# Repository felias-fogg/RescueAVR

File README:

This Arduino sketch is an alternative firmware for manekinen's Fusebit
Doctor PCB (see http://mdiy.pl/atmega-fusebit-doctor-hvpp/?lang=en). The
functionality is very similar. However, it is Open Source (under the
GPL)  and can be freely modified and extended.

You can install the firmware by simply uploading the HEX file to an
ATmega328(P) and deactivating the fuse CKDIV8, so that the chip runs
on 8MHz. Now you are all set.

You can either use the board interactively or stand alone. 

Stand alone mode: After power-up, all LEDs are off and you can insert
a chip. After pressing the button, the board will first try to
recognize the chip. If successful, the green LED will be on for 3
secs, if unsuccessful (chip unknown or completely broken), the red
light will be on for 3 secs. In the rare case that the chip is known,
but we do not know the default fuses, first the green LED is on for 1
second, then the red LED is on for 3 seconds. After that, the board
tries to reset all lock bits and then tries to set the fuses to a safe
default setting. If successful, the green LED blinks, otherwise the
red LED blinks. If unsuccessful, you can try to set the erase jumper,
which allows for erasing the entire chip in order to recover it.

Interactive mode: Set your terminal to 19200 baud, no parity, 1
stop-bit. The board tries to recognize the chip after pressing the
button and then allows you to interactively change any fuse or lock,
to reset the fuses to its default value, or to erase the chip. If the
chip is unknown, it will still recogize a chip signature. If you know
how many fuse bytes the chip has, you can specify that and continue
from there in order to manually change the fuses to desirable values
(look into the manual!). If the board cannot detect any chip, you
still can try to send the commands to the chip. Specify the protocol:
HVPP for all ATmega chips, HVPP for Tiny for all MCUs from the
ATtiny2313 and ATtiny26(1) family, and HVSP for all the other ATtiny
chips. 

If you want to change the firmware, you can do this using the Arduino
IDE. In order to do so, you first need to install a bootloader. Since
the ATmega is running on 8 MHz, you need to use the bootloader
ATmegaBOOT_168_atmega328_pro_8MHz.hex (for your ATmega328P) or
ATmegaBOOT_168_pro_8MHz.hex (if you use an ATmega168). You also should
set the fuse BOOTRST (enabling the boot reset vector) and set the boot
loader size to 2048 bytes in the fuses. Now you can put the chip onto
the fusebit doctor board and connect via a serial line to your
computer. Once you have registered this serial line with your Arduino
IDE and have chosen "Arduino Pro or Pro Mini (3.3V 8MHz) w/ ATmega328"
as the board you want to work with, you can start to download sketches
to the board. Note that you always have to press the reset button in
order to enable the transfer of the program from your computer to the
chip. The timing is critical here. Press the button immediately after
the compiler has finished its work!

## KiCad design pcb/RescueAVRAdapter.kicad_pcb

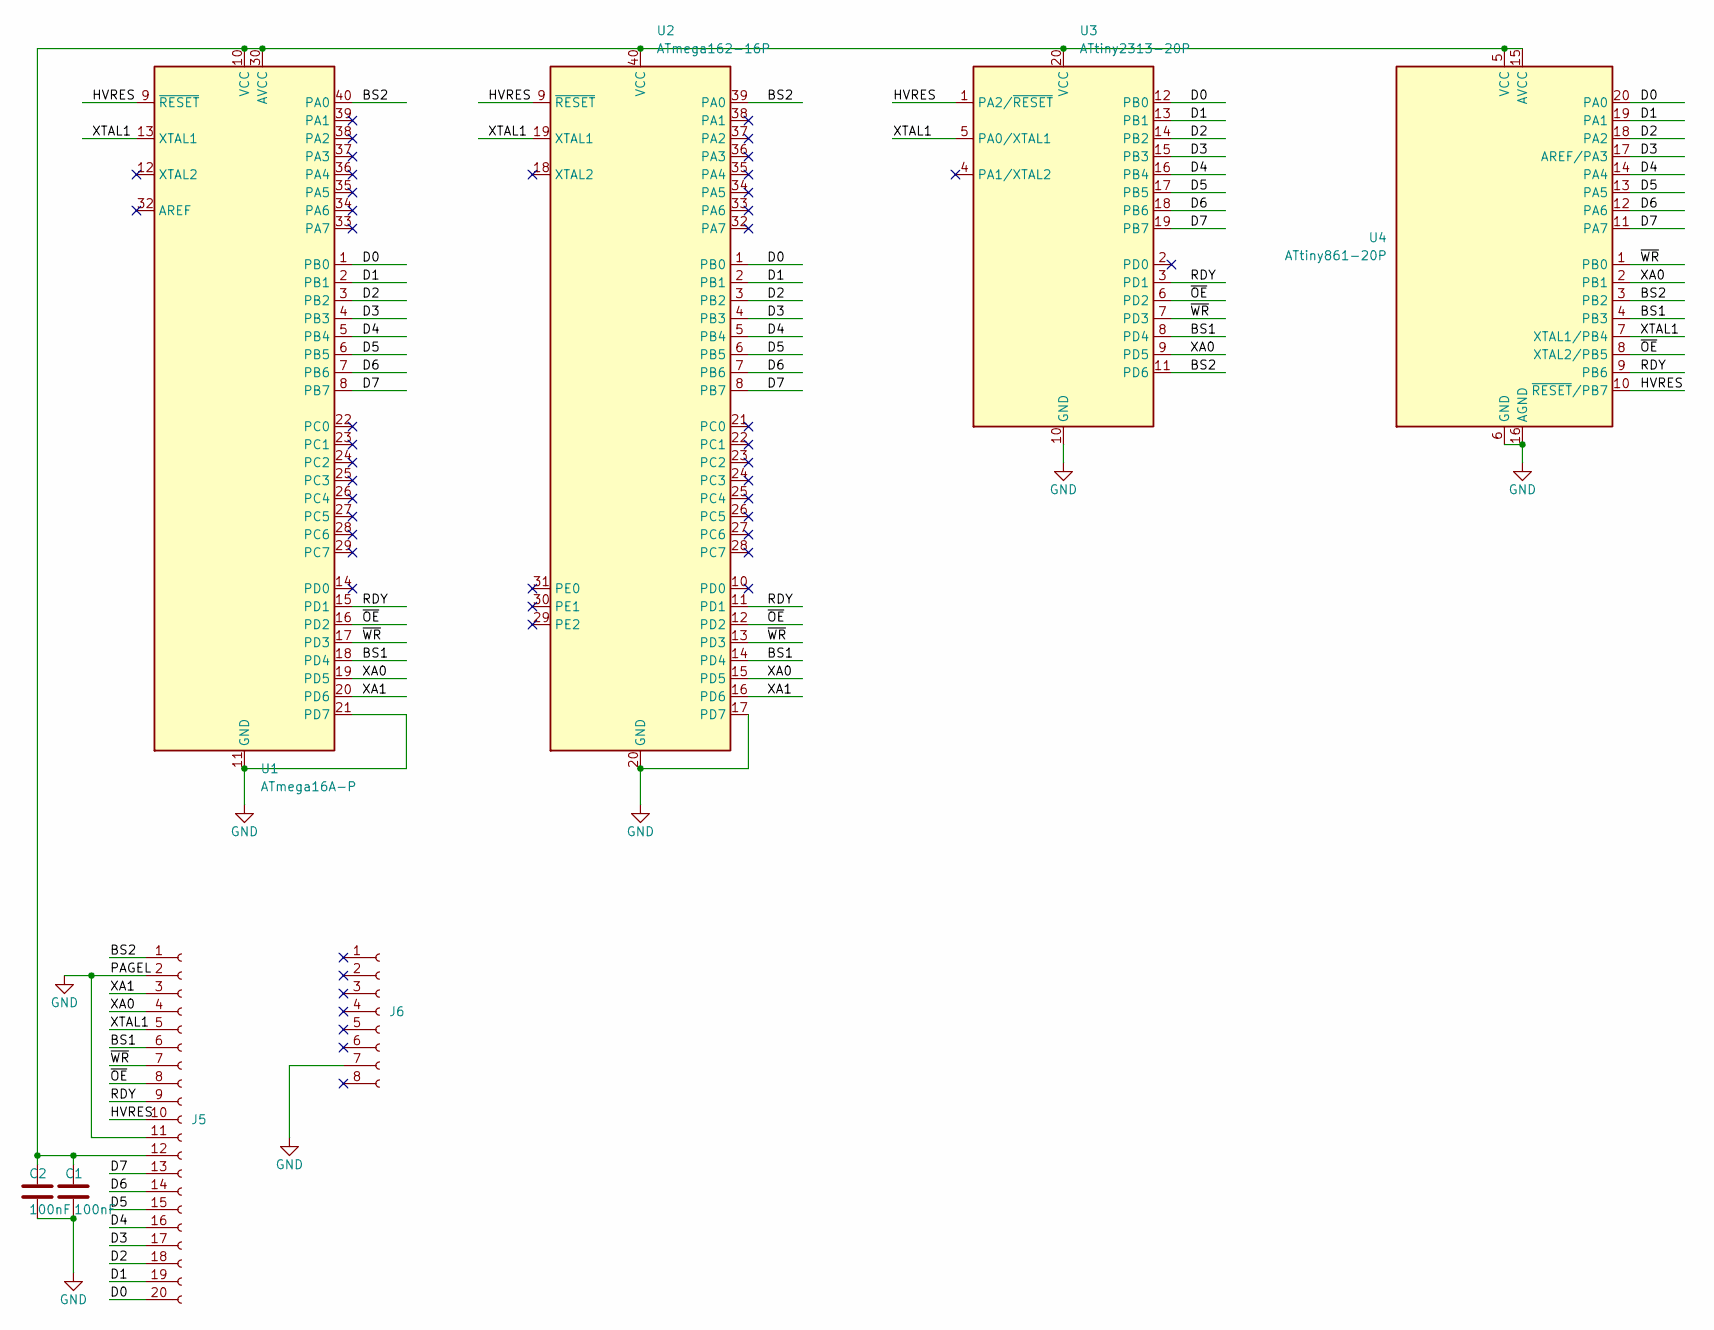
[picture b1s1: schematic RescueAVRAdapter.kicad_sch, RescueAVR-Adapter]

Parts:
C1, C2: 100nF; C_Disc_D7.5mm_W2.5mm_P5.00mm
J5: Conn_01x20_Socket; PinHeader_1x20_P2.54mm_Vertical
J6: Conn_01x08_Socket; PinHeader_1x08_P2.54mm_Vertical
U1: ATmega16A-P; DIP-40_W15.24mm_Socket
U2: ATmega162-16P; DIP-40_W15.24mm_Socket
U3: ATtiny2313-20P; DIP-20_W7.62mm_Socket
U4: ATtiny861-20P; DIP-20_W7.62mm_Socket

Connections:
/BS1: J5.6, U1.18 (PD4), U2.14 (PD4), U3.8 (PD4), U4.4 (PB3)
/BS2: J5.1, U1.40 (PA0), U2.39 (PA0), U3.11 (PD6), U4.3 (PB2)
/D0: J5.20, U1.1 (PB0), U2.1 (PB0), U3.12 (PB0), U4.20 (PA0)
/D1: J5.19, U1.2 (PB1), U2.2 (PB1), U3.13 (PB1), U4.19 (PA1)
/D2: J5.18, U1.3 (PB2), U2.3 (PB2), U3.14 (PB2), U4.18 (PA2)
/D3: J5.17, U1.4 (PB3), U2.4 (PB3), U3.15 (PB3), U4.17 (AREF/PA3)
/D4: J5.16, U1.5 (PB4), U2.5 (PB4), U3.16 (PB4), U4.14 (PA4)
/D5: J5.15, U1.6 (PB5), U2.6 (PB5), U3.17 (PB5), U4.13 (PA5)
/D6: J5.14, U1.7 (PB6), U2.7 (PB6), U3.18 (PB6), U4.12 (PA6)
/D7: J5.13, U1.8 (PB7), U2.8 (PB7), U3.19 (PB7), U4.11 (PA7)
/HVRES: J5.10, U1.9 (~RESET), U2.9 (~RESET), U3.1 (PA2/~RESET), U4.10 (~RESET/PB7)
/RDY: J5.9, U1.15 (PD1), U2.11 (PD1), U3.3 (PD1), U4.9 (PB6)
/XA0: J5.4, U1.19 (PD5), U2.15 (PD5), U3.9 (PD5), U4.2 (PB1)
/XA1: J5.3, U1.20 (PD6), U2.16 (PD6)
/XTAL1: J5.5, U1.13 (XTAL1), U2.19 (XTAL1), U3.5 (PA0/XTAL1), U4.7 (XTAL1/PB4)
/~OE: J5.8, U1.16 (PD2), U2.12 (PD2), U3.6 (PD2), U4.8 (XTAL2/PB5)
/~WR: J5.7, U1.17 (PD3), U2.13 (PD3), U3.7 (PD3), U4.1 (PB0)
GND: C1.2, C2.2, J5.2, J5.11, J6.7, U1.11 (GND), U1.21 (PD7), U1.31 (GND), U2.17 (PD7), U2.20 (GND), U3.10 (GND), U4.6 (GND), U4.16 (AGND)
unnamed: C1.1, C2.1, J5.12, U1.10 (VCC), U1.30 (AVCC), U2.40 (VCC), U3.20 (VCC), U4.5 (VCC), U4.15 (AVCC)

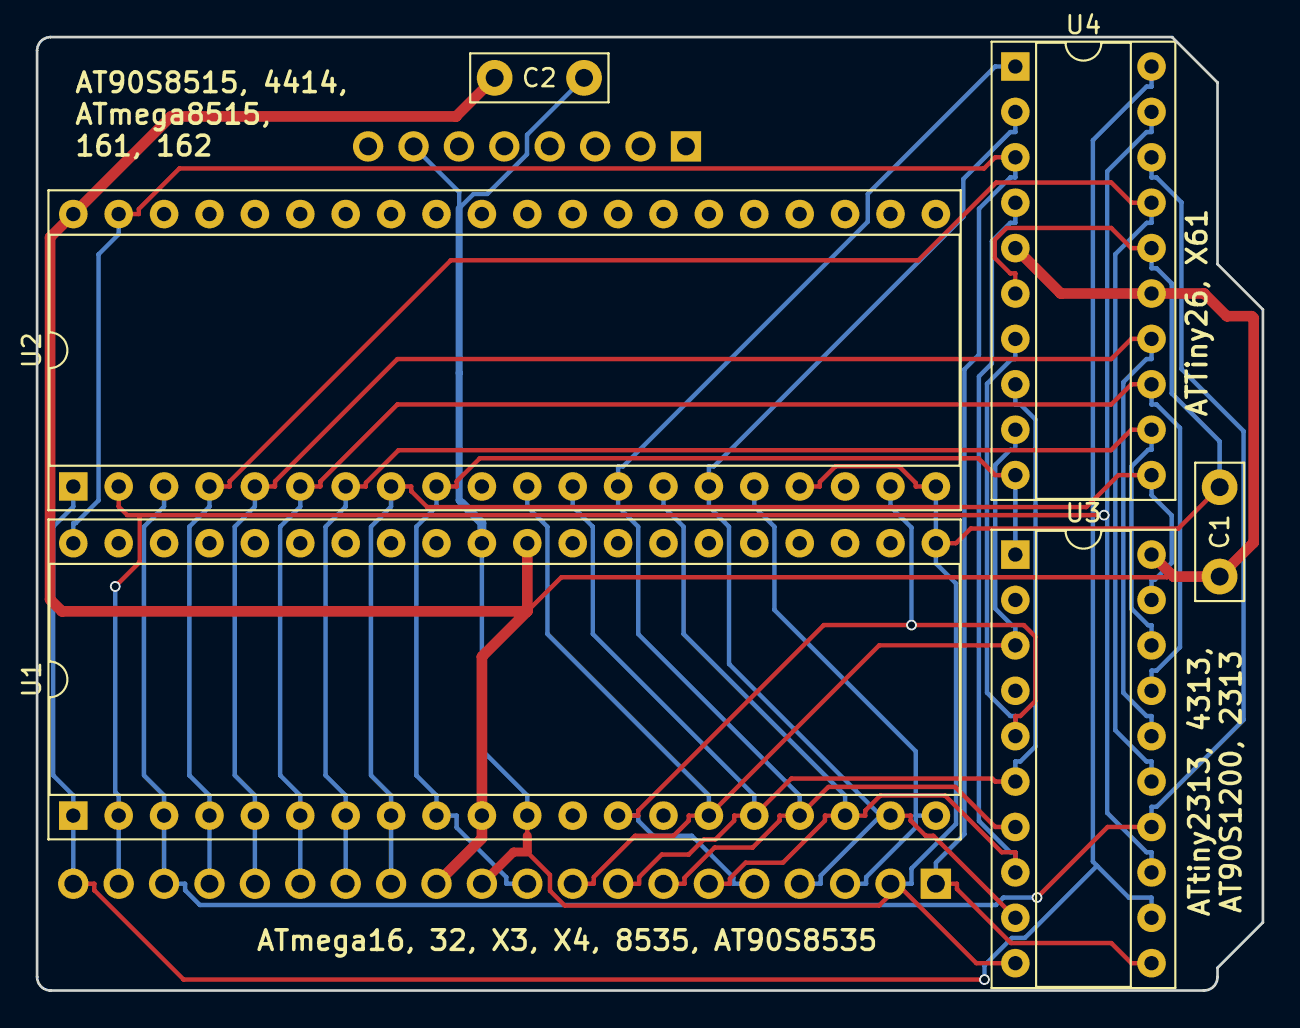
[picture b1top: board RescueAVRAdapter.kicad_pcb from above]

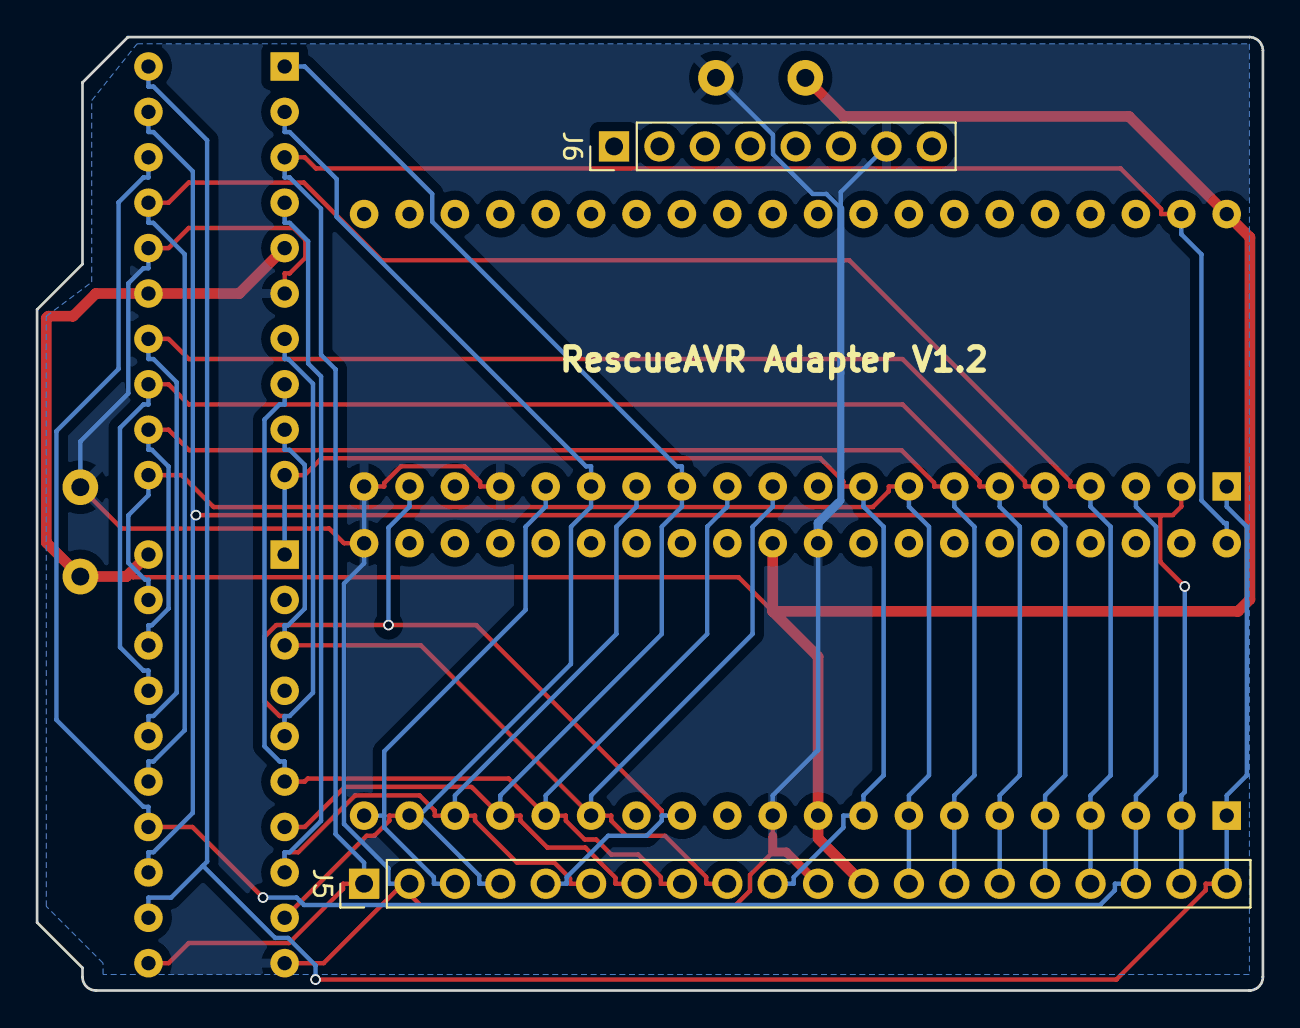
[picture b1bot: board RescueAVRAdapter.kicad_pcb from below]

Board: 2 copper layers, 68.6 x 53.3 mm, 8 parts (2 on the bottom side), 19 nets.

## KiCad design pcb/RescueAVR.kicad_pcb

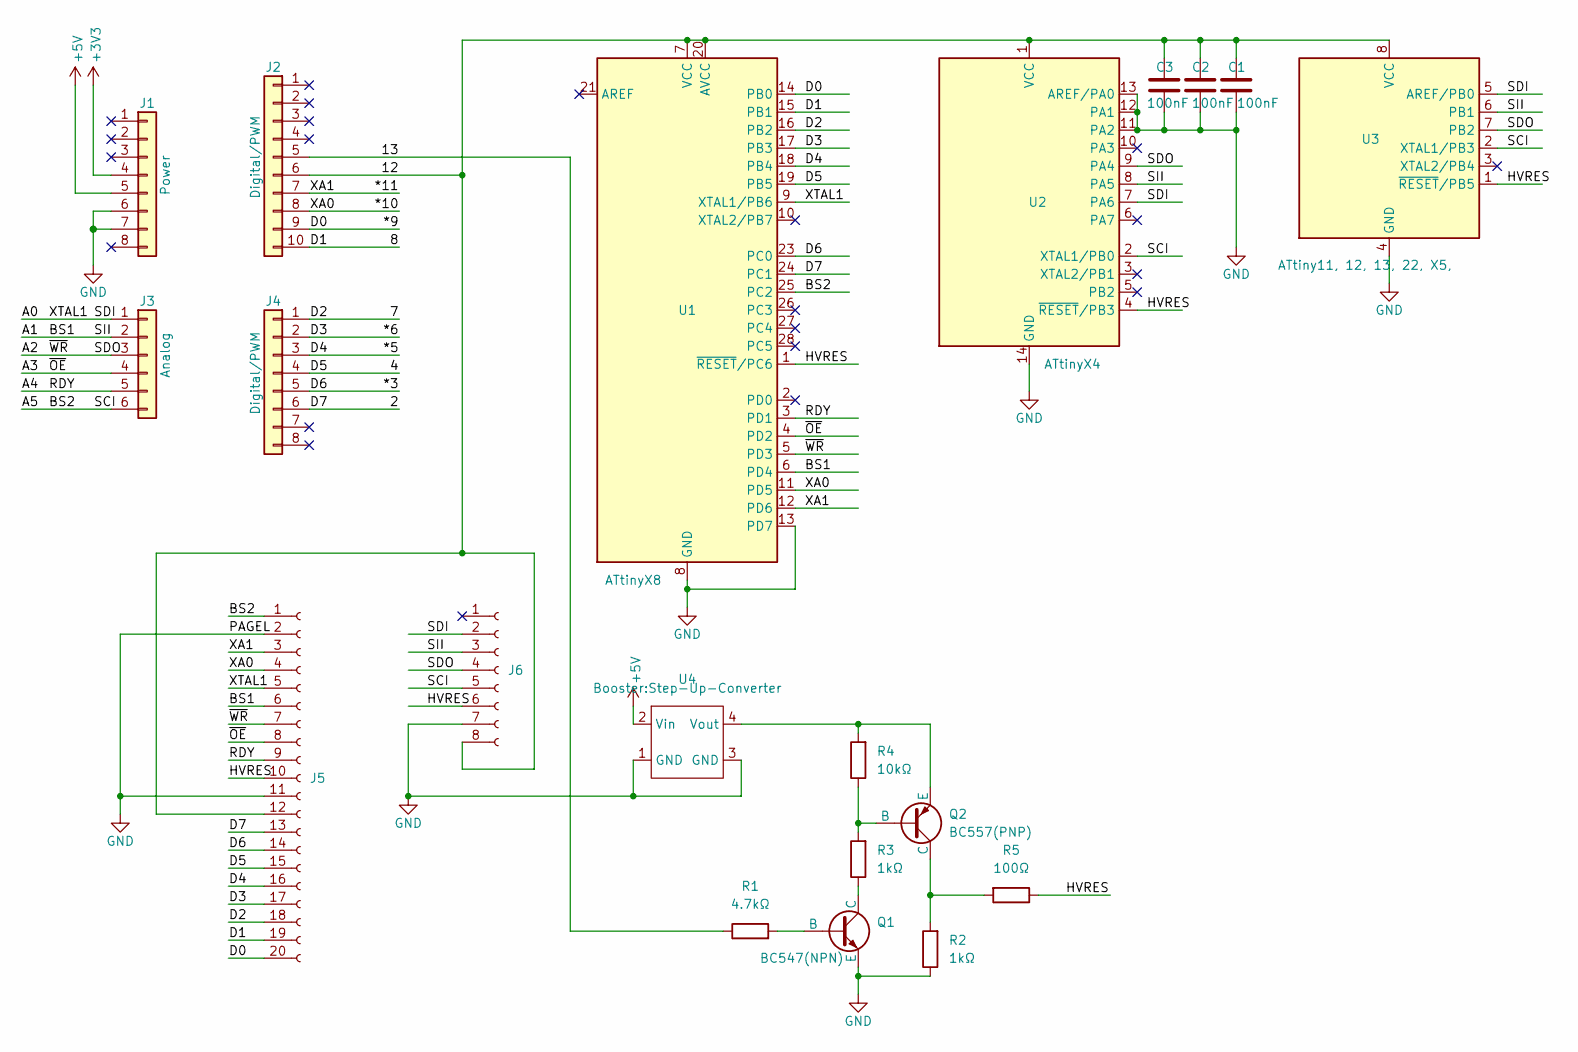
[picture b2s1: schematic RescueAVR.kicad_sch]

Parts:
C1, C2, C3: 100nF; C_Disc_D7.5mm_W2.5mm_P5.00mm
J1: Power; PinHeader_1x08_P2.54mm_Vertical
J2: Digital/PWM; PinHeader_1x10_P2.54mm_Vertical
J3: Analog; PinHeader_1x06_P2.54mm_Vertical
J4: Digital/PWM; PinHeader_1x08_P2.54mm_Vertical
J5: Conn_01x20_Socket; PinSocket_1x20_P2.54mm_Vertical
J6: Conn_01x08_Socket; PinSocket_1x08_P2.54mm_Vertical
Q1: BC547(NPN); TO-92
Q2: BC557(PNP); TO-92
R1: 4.7kΩ; R_Axial_DIN0204_L3.6mm_D1.6mm_P7.62mm_Horizontal
R2, R3: 1kΩ; R_Axial_DIN0204_L3.6mm_D1.6mm_P7.62mm_Horizontal
R4: 10kΩ; R_Axial_DIN0204_L3.6mm_D1.6mm_P7.62mm_Horizontal
R5: 100Ω; R_Axial_DIN0204_L3.6mm_D1.6mm_P7.62mm_Horizontal
U1: ATtinyX8; DIP-28_W7.62mm_Socket
U2: ATtinyX4; DIP-14_W7.62mm_Socket
U3: ATtiny11, 12, 13, 22, X5,; DIP-8_W7.62mm_Socket
U4: Step-Up-Converter

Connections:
+3V3: J1.4
+5V: J1.5, U4.2 (Vin)
/2: J4.6, J5.13, U1.24 (PC1)
/4: J4.4, J5.15, U1.19 (PB5)
/7: J4.1, J5.18, U1.16 (PB2)
/8: J2.10, J5.19, U1.15 (PB1)
/12: C1.1, C2.1, C3.1, J2.6, J5.12, J6.8, U1.7 (VCC), U1.20 (AVCC), U2.1 (VCC), U3.8 (VCC)
/13: J2.5, R1.1
/*3: J4.5, J5.14, U1.23 (PC0)
/*5: J4.3, J5.16, U1.18 (PB4)
/*6: J4.2, J5.17, U1.17 (PB3)
/*9: J2.9, J5.20, U1.14 (PB0)
/*10: J2.8, J5.4, U1.11 (PD5)
/*11: J2.7, J5.3, U1.12 (PD6)
/A0: J3.1, J5.5, J6.2, U1.9 (XTAL1/PB6), U2.7 (PA6), U3.5 (AREF/PB0)
/A1: J3.2, J5.6, J6.3, U1.6 (PD4), U2.8 (PA5), U3.6 (PB1)
/A2: J3.3, J5.7, J6.4, U1.5 (PD3), U2.9 (PA4), U3.7 (PB2)
/A3: J3.4, J5.8, U1.4 (PD2)
/A4: J3.5, J5.9, U1.3 (PD1)
/A5: J3.6, J5.1, J6.5, U1.25 (PC2), U2.2 (XTAL1/PB0), U3.2 (XTAL1/PB3)
/HVRES: J5.10, J6.6, R5.1, U1.1 (~RESET/PC6), U2.4 (~RESET/PB3), U3.1 (~RESET/PB5)
GND: C1.2, C2.2, C3.2, J1.6, J1.7, J5.2, J5.11, J6.7, Q1.3 (E), R2.1, U1.8 (GND), U1.13 (PD7), U1.22 (GND), U2.11 (PA2), U2.12 (PA1), U2.13 (AREF/PA0), U2.14 (GND), U3.4 (GND), U4.1 (GND), U4.3 (GND)
unnamed: Q1.2 (B), R1.2
unnamed: Q1.1 (C), R3.1
unnamed: Q2.2 (B), R3.2, R4.1
unnamed: Q2.1 (C), R2.2, R5.2
unnamed: Q2.3 (E), R4.2, U4.4 (Vout)

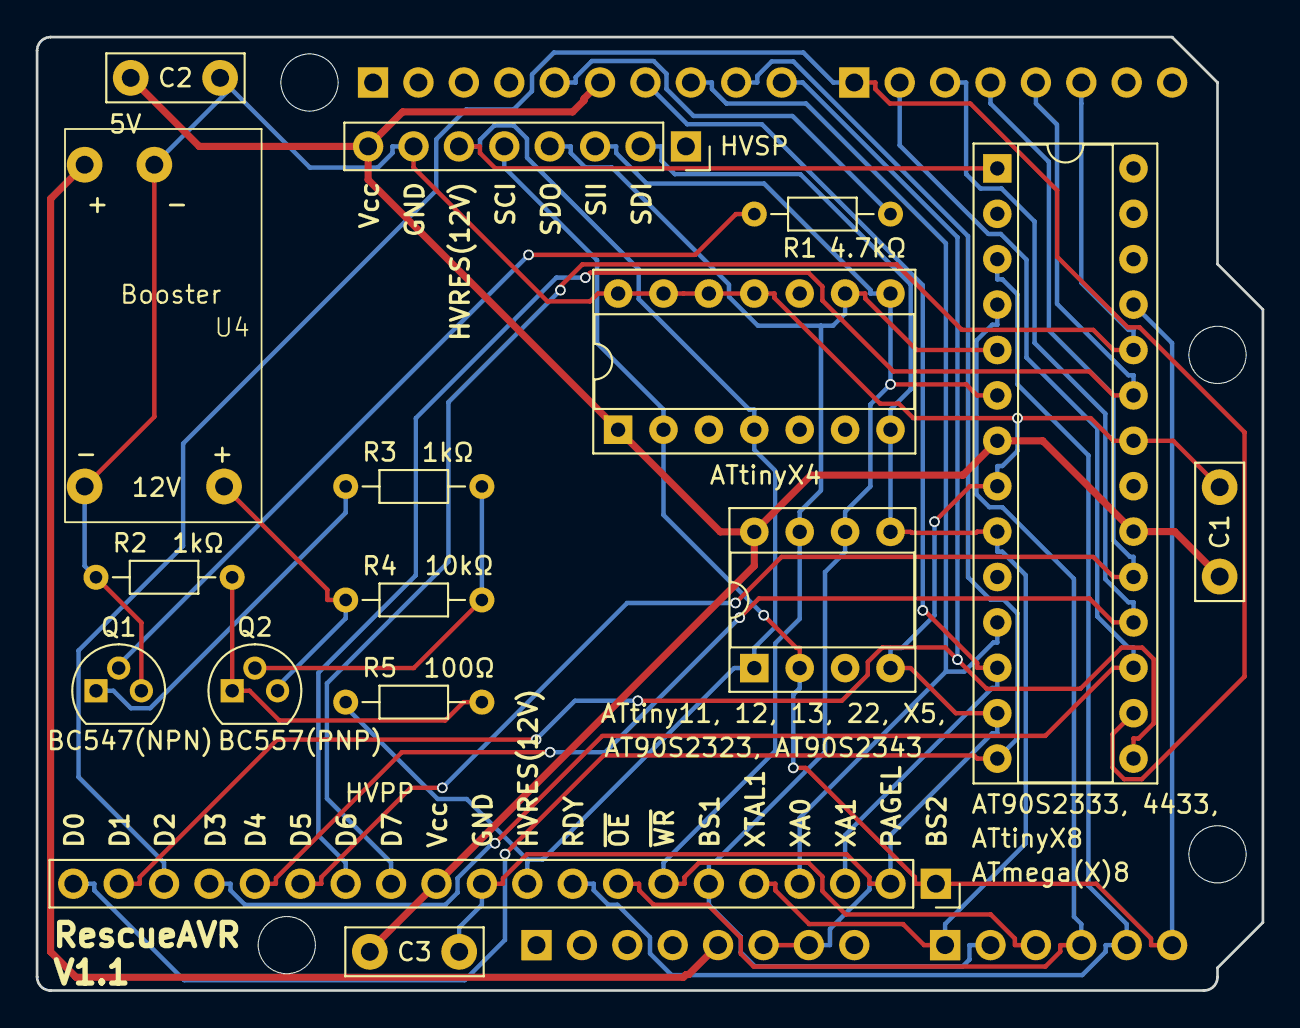
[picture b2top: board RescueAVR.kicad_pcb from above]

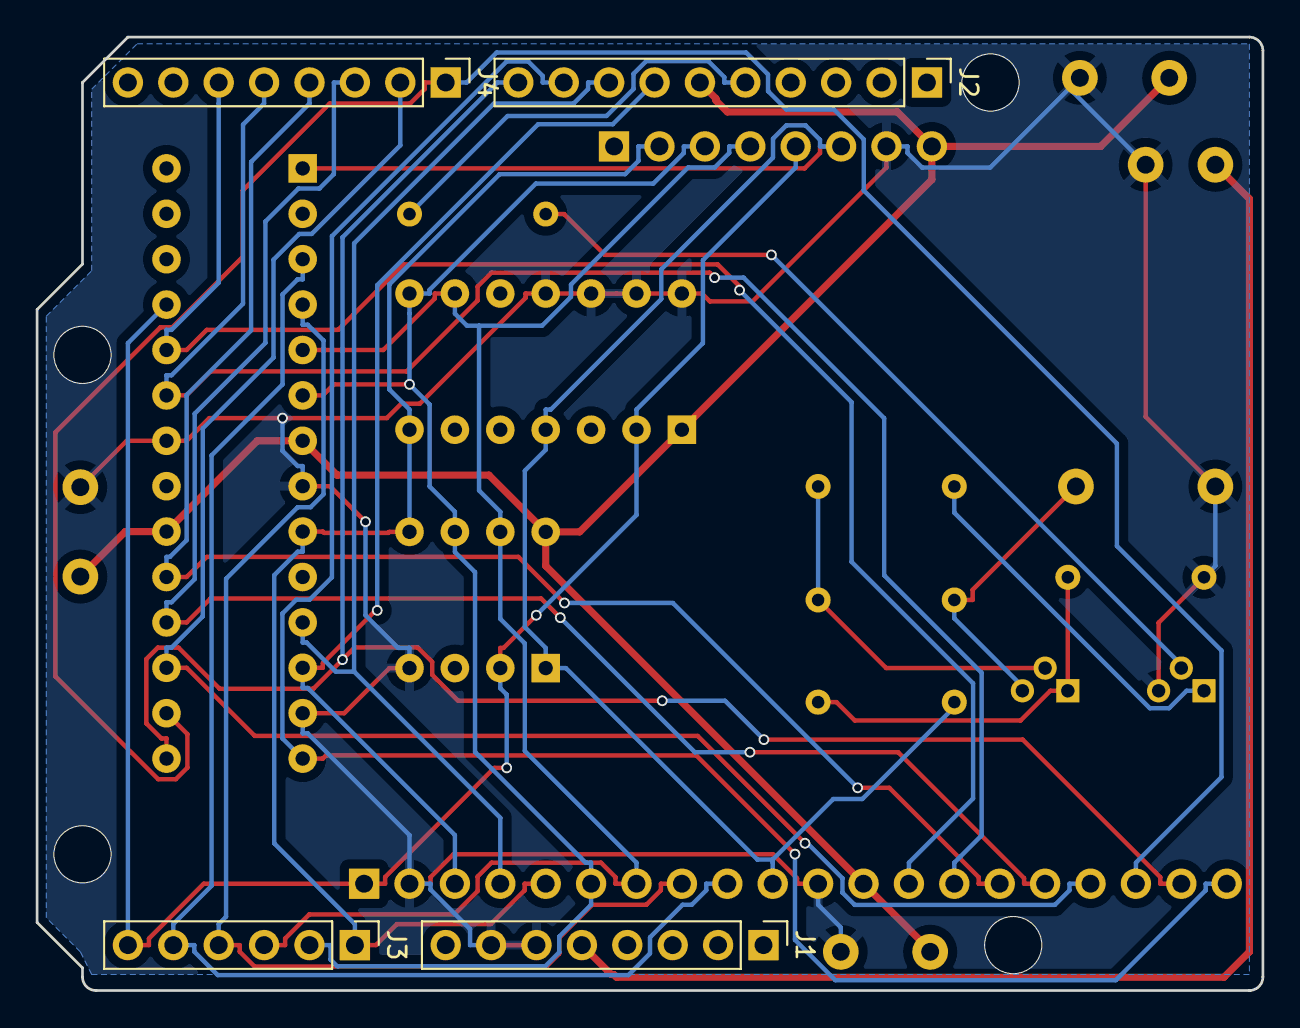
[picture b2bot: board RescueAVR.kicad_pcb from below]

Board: 2 copper layers, 68.6 x 53.3 mm, 24 parts (4 on the bottom side), 26 nets.

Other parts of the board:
MH1, MH2, MH3, MH4: MountingHole_3.2mm

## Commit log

2013-10-01 Small changes in README file
2013-10-01 changes to read + generated MCU list
2013-10-01 Version 0.91 - added a few addtional MCUs
2013-10-01 Version 0.93 - a few correction & reordering of table
2013-10-01 and the new hex file for 0.93
2013-10-01 Version 0.94
    - wrong version number
    - green LED did not work in conjunction with Tiny HVPP
    - added some diagnostic message for non-int. mode
2013-10-01 README updatet
2013-10-01 additional commit of Version 0.94
2013-10-01 no schort description
2013-10-01 readme changed
2013-10-01 again readme change
2013-10-01 readme again
2013-10-01 readme - last time
2013-10-04 Version 2.0
    - nicer UI
    - now, it can also be used on an Arduino
    - added Fritzing wiring sketches
2013-10-04 Fritzing files added
2013-10-04 new hex file + DEBUG code removed
2013-11-10 V2.1
    Added: Show OSCCAL register
2018-02-05 Add const keyword to all PROGMEM variables
    Modern versions of AVR-GCC require that all PROGMEM variables be declared const. Without these keywords the sketch does not compile when using any recent version of Arduino AVR Boards, etc.:
    RescueAVR:58: error: variable 'at90s2313' must be const in order to be put into read-only section by means of '__attribute__((progmem))'
2021-01-21 V2.3:
    Added ATtiny1634, corrected code for reading OSCCAL values, added 'R'
    to all menus to trigger a reset, and cleaned up the docu
2021-07-21 typo
2021-11-14 Changes in README
2022-01-25 V2.3.1
2022-01-25 readme typos corrected
2022-01-25 readme fix
2024-08-20 V2.4.0
2024-08-28 V2.5.0
2024-08-28 V2.6.0
2024-08-28 readme update
2024-08-28 readme
2024-08-28 pictures
2024-08-28 pics
2024-09-05 V2.6.0 and new PCBs
2024-09-05 manual
2024-09-06 fixed pic URLs in manual
2024-09-07 Tindie
2024-09-08 V2.7.0
2024-09-09 V3.0.0
2024-09-09 V3.0.1
2024-09-10 V3.0.2
2024-09-28 V3.1.0
2024-09-29 README.md aktualisieren
2025-03-03 V3.1.1 - faster startup
